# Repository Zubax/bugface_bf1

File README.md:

# Zubax BugFace BF1

Zubax BugFace BF1 (formerly known as Dronecode Probe) is a generic JTAG/SWD+UART console adapter compatible with most ARM Cortex based designs and in particular with the hardware maintained by the [Dronecode project](http://dronecode.org/).

The design is based on Black Magic Probe and is distributed under open source licenses. The full description of its features and supported targets can be found at the [Black Magic Probe homepage](https://black-magic.org/).

For the manufacturing instructions refer to [MANUFACTURING.md](MANUFACTURING.md).

## Features

- Some of the supported targets include:
  - STMicroelectronics STM32
  - Microchip/Atmel SAM
  - NXP LPC/Kinetis
  - Texas Instruments LM/TM
  - Silicon Labs EFM32/EZR32
  - Xilinx Zynq-7000
  - Broadcom BCM2836
  - **And many others!** See the [Black Magic Probe homepage](https://black-magic.org/) for the full list of supported targets.

- Embedded GDB server on the device. No host-side driver needed (this is unlike, for example, OpenOCD).
  - Loading the application into flash or RAM.
  - Real-time execution and single-stepping.
  - Hardware assisted breakpoints and read/write/access watchpoints.
  - Software breakpoints when executing from RAM.

- Simple integration with development tools and IDE.
- Connectors are compatible with the Dronecode Autopilot Connector Standard.
- Optional power supply delivery to the target (the power is sourced from USB).

## USB interface

BF1 is a composite USB device that incorporates two virtual serial port interfaces:

1. The first virtual serial port interface is connected to the debugger's embedded GDB server; this interface is used by the host-side debugger to interact with the target. The baud rate and other parameters of a typical serial port are irrelevant for this interface, because it has no physical representation.

2. The second virtual serial port interface is connected to the physical UART interface that can be used to communicate directly with the target's application (for example, this can be used to access the [Serial command line interface (Serial CLI)](https://wiki.zubax.com/public/serial-cli) on the target).

For example, the host may represent the debugger as follows:

- `COM3` (on Windows), or `/dev/serial/by-id/usb-Black_Magic_Debug_Black_Magic_Probe_v1.10.0-836-g254bc265-dirty_C0E079F1-if00` (on GNU/Linux) - this is the GDB interface.
- `COM4` (on Windows), or `/dev/serial/by-id/usb-Black_Magic_Debug_Black_Magic_Probe_v1.10.0-836-g254bc265-dirty_C0E079F1-if02` (on GNU/Linux) - this is the physical UART interface that can be used to interact with the target's application (e.g. a serial CLI).

The device does not require drivers since it uses the standard USB CDC ACM profile. If you're using the device with GNU/Linux, be sure [configure the access permissions correctly](https://wiki.zubax.com/en/public/USB/Using-USB-devices-with-GNULinux).

The USB Vendor ID (VID) is **0x1D50**, and the Product ID (PID) is **0x6018**.

## Connectors

This section documents the available debug interfaces and their connectors, except for the micro-USB since its purpose is evident.

### DCD-M

The DCD-M connector pinout is documented in the table below. It exposes both SWD and UART interfaces to the target, where UART is typically used to access the debug serial console of the target.

| Pin     | Type     | Name     | Comment           |
| ------- | -------- | -------- | ----------------- |
| 1       | IN       | `TPWR`   | Target power sense; also can be used to power the target. |
| 2       | IN       | `UART_RX`| Serial input.     |
| 3       | OUT      | `UART_TX`| Serial output.    |
| 4       | IN/OUT   | `SWDIO`  | SWD data line.    |
| 5       | OUT      | `SWDCLK` | SWD clock line.   |
| 6       | GND      | `GND`    |                   |

The connector part numbers are as follows:

| Name      | Manufacturer  | Part number                                                           | Pitch | Datasheet     |
| --------- | ------------- | --------------------------------------------------------------------- | ------| ------------- |
| DCD-M     | JST           | **BM06B-SRSS-TB** *(top entry)*, or **SM06B-SRSS-TB** *(side entry)*  | 1 mm  | [http://www.jst-mfg.com/product/pdf/eng/eSH.pdf](http://www.jst-mfg.com/product/pdf/eng/eSH.pdf) |

### ARM Cortex M debug connector

This is the standard ARM Cortex M debug connector that can be seen on many other ARM debuggers.

| Pin | Name            |
| --- | --------------- |
| 1   | `TPWR`          |
| 2   | `SWDIO/TMS`     |
| 3   | `GND`           |
| 4   | `SWDCLK/TCK`    |
| 5   | `GND`           |
| 6   | `SWO/TDO`       |
| 7   |                 |
| 8   | `NC/TDI`        |
| 9   | `GND`           |
| 10  | `nRESET`        |

### Pixhawk v1 serial

This connector exposes only the UART interface. It can be used as a general UART port, and its pinout is compatible with the debug serial port on the Pixhawk v1 autopilot.

| Pin | Type        | Name      | Comment   |
| --- | ----------- | --------- | --------- |
| 1   | Power OUT   | `5V`      | Optional 5 V supply output to the target directly from USB.<br><br>Disabled by default; refer to the schematic to see what hardware modifications are required to enable it. |
| 2   |             |           | Not used          |
| 3   |             |           | Not used          |
| 4   | IN          | `UART_RX` | Serial input      |
| 5   | OUT         | `UART_TX` | Serial output     |
| 6   | GND         | GND       |                   |

## Updating the device's own firmware

Please refer to the following sources:

- <https://black-magic.org/upgrade.html>
- [MANUFACTURING.md](MANUFACTURING.md)

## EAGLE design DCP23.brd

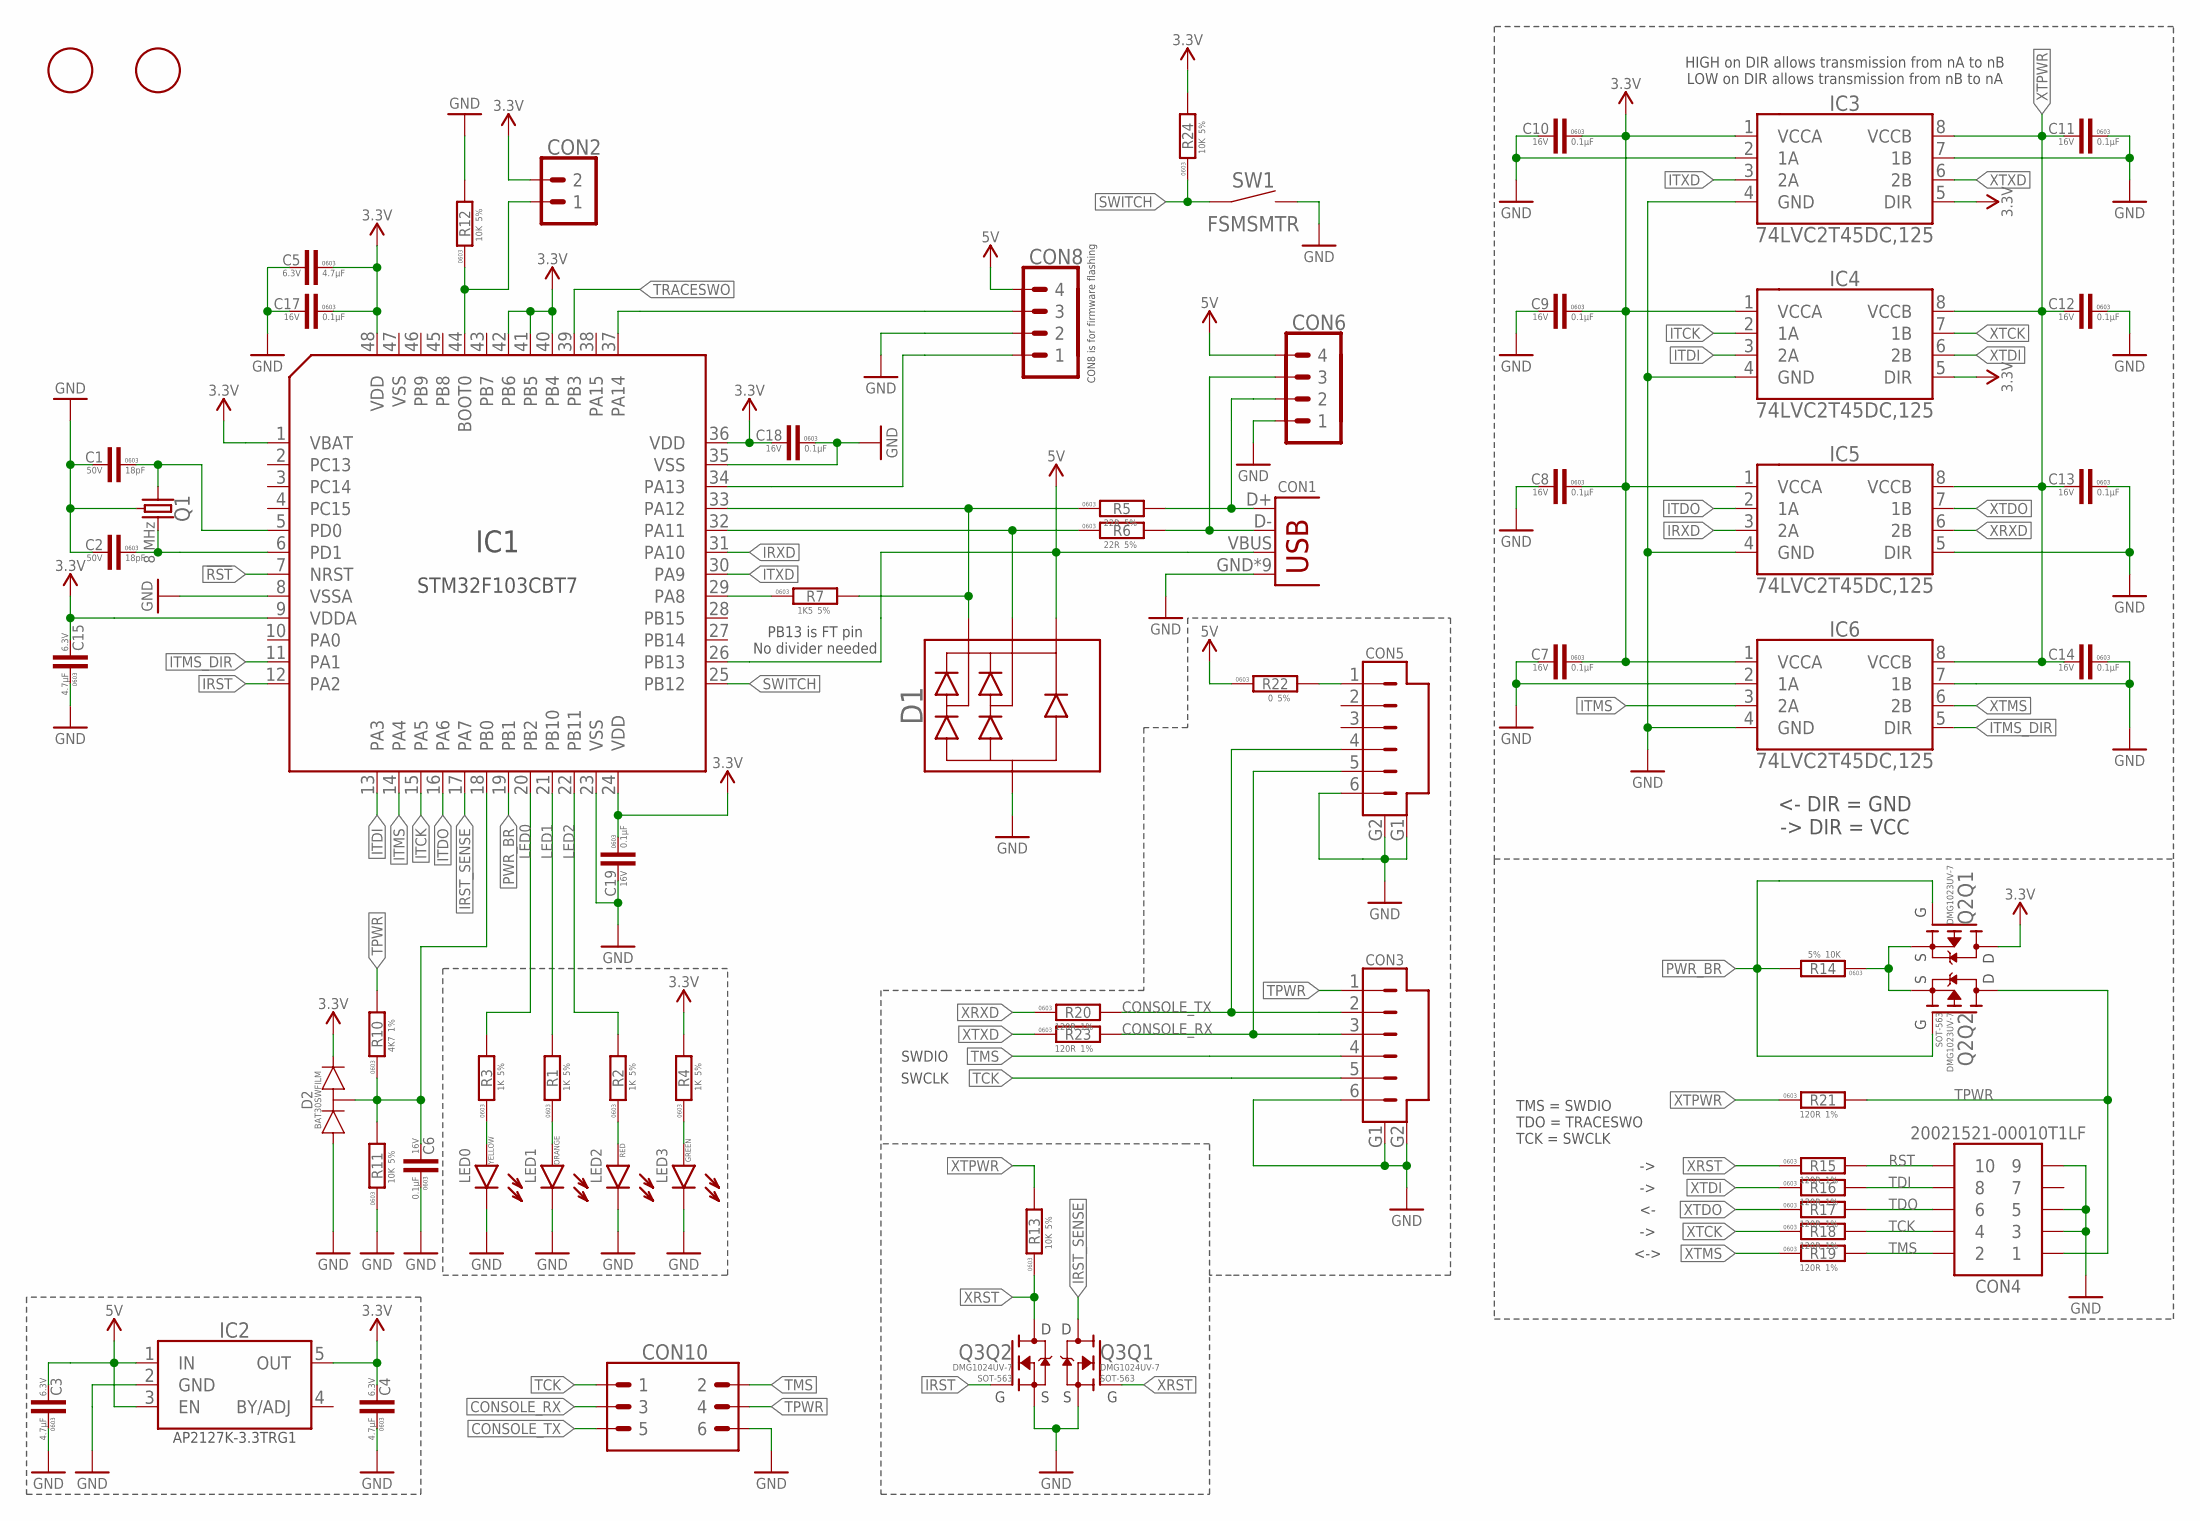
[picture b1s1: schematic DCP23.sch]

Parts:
C1, C2: 18pF; C0603
C3, C4, C5, C15: 4.7µF; C0603
C6, C7, C8, C9, C10, C11, C12, C13, C14, C17, C18, C19: 0.1µF; C0603
CON1: USB-1; MICRO_USB_WITH_PEGS
CON2: PINHEAD_1X02-2; 1X02-PTH-2
CON3: CON-6P-SM06B; SM06B
CON4: CON-2X5P; 200215-00010T1LF
CON5: CON-6P-DF13; DF13C-6P-1.25V
CON6, CON8: PINHEAD_1X04-2.54; 1X04-PTH-2.54
CON10: PINHEAD_2X03-PTH-2.54; 2X03-PTH-2.54
D1: PRTR5V0U2X; SOT143B
D2: BAT30SWFILM; SC70
IC1: STM32F103CBT7; LQFP48
IC2: AP2127-3.3; SOT23-5
IC3, IC4, IC5, IC6: 74LVC2T45; VSSOP8
LED0: LED-0603; LED0603; DIGIKEY# 160-1448-1-ND
LED1: LED-0603; LED0603; DIGIKEY# 160-1445-1-ND
LED2: LED-0603; LED0603; DIGIKEY# SML-D12U1WT86CT-ND
LED3: LED-0603; LED0603; DIGIKEY# 160-1446-1-ND
Q1: 8 MHz; OSCILLATOR-5.0X3.2-4P
Q2: DMG1023UV-7; SOT-563
Q3: DMG1024UV-7; SOT-563
R1, R2, R3, R4: 1K; R0603
R5, R6: 22R; R0603; DIGIKEY# 311-22NCT-ND
R7: 1K5; R0603; DIGIKEY# 311-1.50KHRCT-ND
R10: 4K7; R0603
R11, R12, R13, R14, R24: 10K; R0603
R15, R16, R17, R18, R19, R20, R21, R23: 120R; R0603
R22: 0; R0603
SW1: TACT_SWITCH-FSMSM; FSMSM
U$9, U$10: FIDUCIALMOUNT; FIDUCIA-MOUNT

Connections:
!RST: IC1.7 (NRST)
CONSOLE_RX: CON3.3, CON5.5, CON10.3, R23.P$2 (2)
CONSOLE_TX: CON3.2, CON5.4, CON10.5, R20.P$2 (2)
GND: C1.P$2 (2), C2.P$2 (2), C3.P$1 (1), C4.P$1 (1), C5.P$2 (2), C6.P$1 (1), C7.P$2 (2), C8.P$2 (2), C9.P$2 (2), C10.P$2 (2), C11.P$1 (1), C12.P$1 (1), C13.P$1 (1), C14.P$1 (1), C15.P$1 (1), C17.P$2 (2), C18.P$1 (1), C19.P$2 (2), CON1.GND, CON1.GND1 (GND), CON1.GND2 (GND), CON1.GND3 (GND), CON1.GND4 (GND), CON1.P$1 (GND), CON1.P$2 (GND), CON1.P$3 (GND), CON1.P$4 (GND), CON3.6, CON3.G1, CON3.G2, CON4.3, CON4.5, CON4.9, CON5.6, CON5.G1 (G2), CON5.G2 (G1), CON6.1, CON8.2, CON10.6, D1.1 (C), D2.1 (A), IC1.8 (VSSA), IC1.23 (VSS), IC1.35 (VSS), IC2.2 (GND), IC3.2 (1A), IC3.4 (GND), IC3.7 (1B), IC4.4 (GND), IC5.4 (GND), IC5.5 (DIR), IC6.2 (1A), IC6.4 (GND), IC6.7 (1B), LED0.C, LED1.C, LED2.C, LED3.C, Q1.2 (GND), Q1.4 (GND), Q3.1 (S), Q3.4 (S), R11.P$1 (1), R12.P$2 (2), SW1.P$2 (2)
IRST: IC1.12 (PA2), Q3.5 (G)
IRST_SENSE: IC1.17 (PA7), Q3.6 (D)
IRXD: IC1.31 (PA10), IC5.3 (2A)
ITCK: IC1.15 (PA5), IC4.2 (1A)
ITDI: IC1.13 (PA3), IC4.3 (2A)
ITDO: IC1.16 (PA6), IC5.2 (1A)
ITMS: IC1.14 (PA4), IC6.3 (2A)
ITMS_DIR: IC1.11 (PA1), IC6.5 (DIR)
ITXD: IC1.30 (PA9), IC3.3 (2A)
LED0: IC1.20 (PB2), R3.P$2 (2)
LED1: IC1.21 (PB10), R1.P$2 (2)
LED2: IC1.22 (PB11), R2.P$2 (2)
unnamed: C1.P$1 (1), IC1.5 (PD0), Q1.1
unnamed: LED0.A, R3.P$1 (1)
unnamed: C2.P$1 (1), IC1.6 (PD1), Q1.3 (2)
unnamed: LED2.A, R2.P$1 (1)
unnamed: LED1.A, R1.P$1 (1)
unnamed: LED3.A, R4.P$1 (1)
unnamed: IC1.29 (PA8), R7.1
unnamed: D1.3 (D2), IC1.32 (PA11), R6.1
unnamed: D1.2 (D1), IC1.33 (PA12), R5.1, R7.2
unnamed: Q2.1 (S), Q2.4 (S), R14.P$1 (1)
unnamed: CON5.1, R22.P$2 (2)
unnamed: CON2.1, IC1.44 (BOOT0), R12.P$1 (1)
PWR_BR: IC1.19 (PB1), Q2.2 (G), Q2.5 (G), R14.P$2 (2)
RST: CON4.10, R15.P$2 (2)
SWCLK: CON8.3, IC1.37 (PA14)
SWDIO: CON8.1, IC1.34 (PA13)
SWITCH: IC1.25 (PB12), R24.P$1 (1), SW1.P$1 (1)
TCK: CON3.5, CON4.4, CON10.1, R18.P$2 (2)
TDI: CON4.8, R16.P$2 (2)
TDO: CON4.6, R17.P$2 (2)
TMS: CON3.4, CON4.2, CON10.2, R19.P$2 (2)
TPWR: CON3.1, CON4.1, CON10.4, Q2.6 (D), R10.P$2 (2), R21.P$2 (2)
TRACESWO: IC1.39 (PB3)
USB_DM: CON1.D-, CON6.3, R6.2
USB_DP: CON1.D+, CON6.2, R5.2
VBUS1: C6.P$2 (2), D2.3 (COMMON), IC1.18 (PB0), R10.P$1 (1), R11.P$2 (2)
VDD_3V3: C4.P$2 (2), C5.P$1 (1), C7.P$1 (1), C8.P$1 (1), C9.P$1 (1), C10.P$1 (1), C15.P$2 (2), C17.P$1 (1), C18.P$2 (2), C19.P$1 (1), CON2.2, D2.2 (C), IC1.1 (VBAT), IC1.9 (VDDA), IC1.24 (VDD), IC1.36 (VDD), IC1.40 (PB4), IC1.41 (PB5), IC1.42 (PB6), IC1.48 (VDD), IC2.5 (OUT), IC3.1 (VCCA), IC3.5 (DIR), IC4.1 (VCCA), IC4.5 (DIR), IC5.1 (VCCA), IC6.1 (VCCA), Q2.3 (D), R4.P$2 (2), R24.P$2 (2)
VDD_5V: C3.P$2 (2), CON1.VBUS, CON6.4, CON8.4, D1.4 (A), IC1.26 (PB13), IC2.1 (IN), IC2.3 (EN), R22.P$1 (1)
XRST: Q3.2 (G), Q3.3 (D), R13.P$1 (1), R15.P$1 (1)
XRXD: IC5.6 (2B), R20.P$1 (1)
XTCK: IC4.7 (1B), R18.P$1 (1)
XTDI: IC4.6 (2B), R16.P$1 (1)
XTDO: IC5.7 (1B), R17.P$1 (1)
XTMS: IC6.6 (2B), R19.P$1 (1)
XTPWR: C11.P$2 (2), C12.P$2 (2), C13.P$2 (2), C14.P$2 (2), IC3.8 (VCCB), IC4.8 (VCCB), IC5.8 (VCCB), IC6.8 (VCCB), R13.P$2 (2), R21.P$1 (1)
XTXD: IC3.6 (2B), R23.P$1 (1)

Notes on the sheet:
<- DIR = GND -> DIR = VCC
TMS = SWDIO TDO = TRACESWO TCK = SWCLK
<->
HIGH on DIR allows transmission from nA to nB LOW on DIR allows transmission from nB to nA
SWDIO
SWCLK
CON8 is for firmware flashing
PB13 is FT pin No divider needed

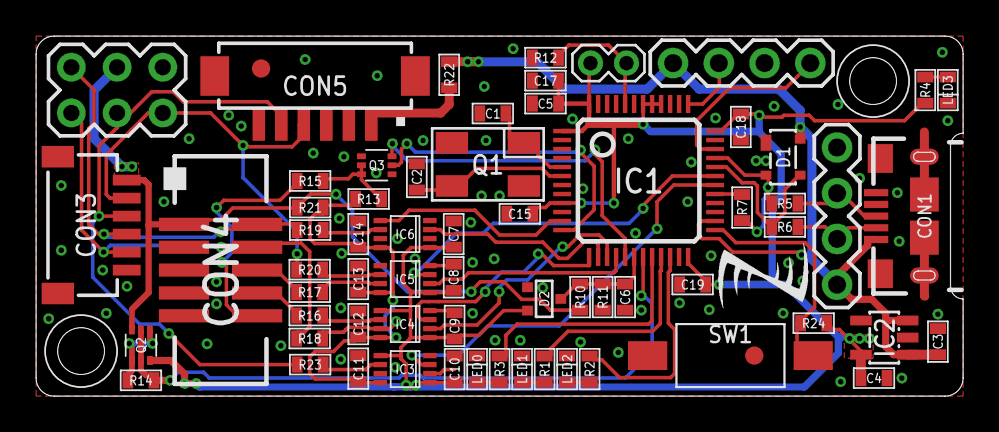
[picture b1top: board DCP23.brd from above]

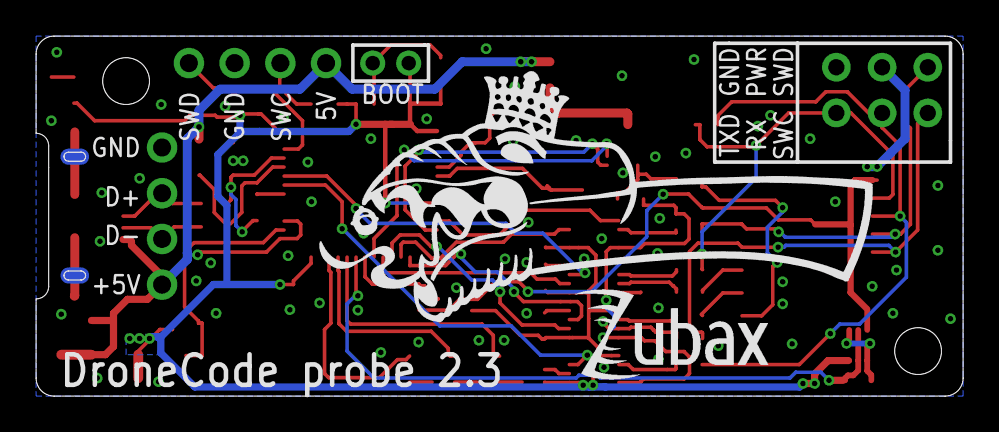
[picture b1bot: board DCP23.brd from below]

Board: 2 copper layers, 51.5 x 20.0 mm, 69 parts (2 on the bottom side), 50 nets.

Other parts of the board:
U$1: DRAGON-30X13
U$2: Z_LOGO_5
U$3: ZUBAX_LOGO_5X10

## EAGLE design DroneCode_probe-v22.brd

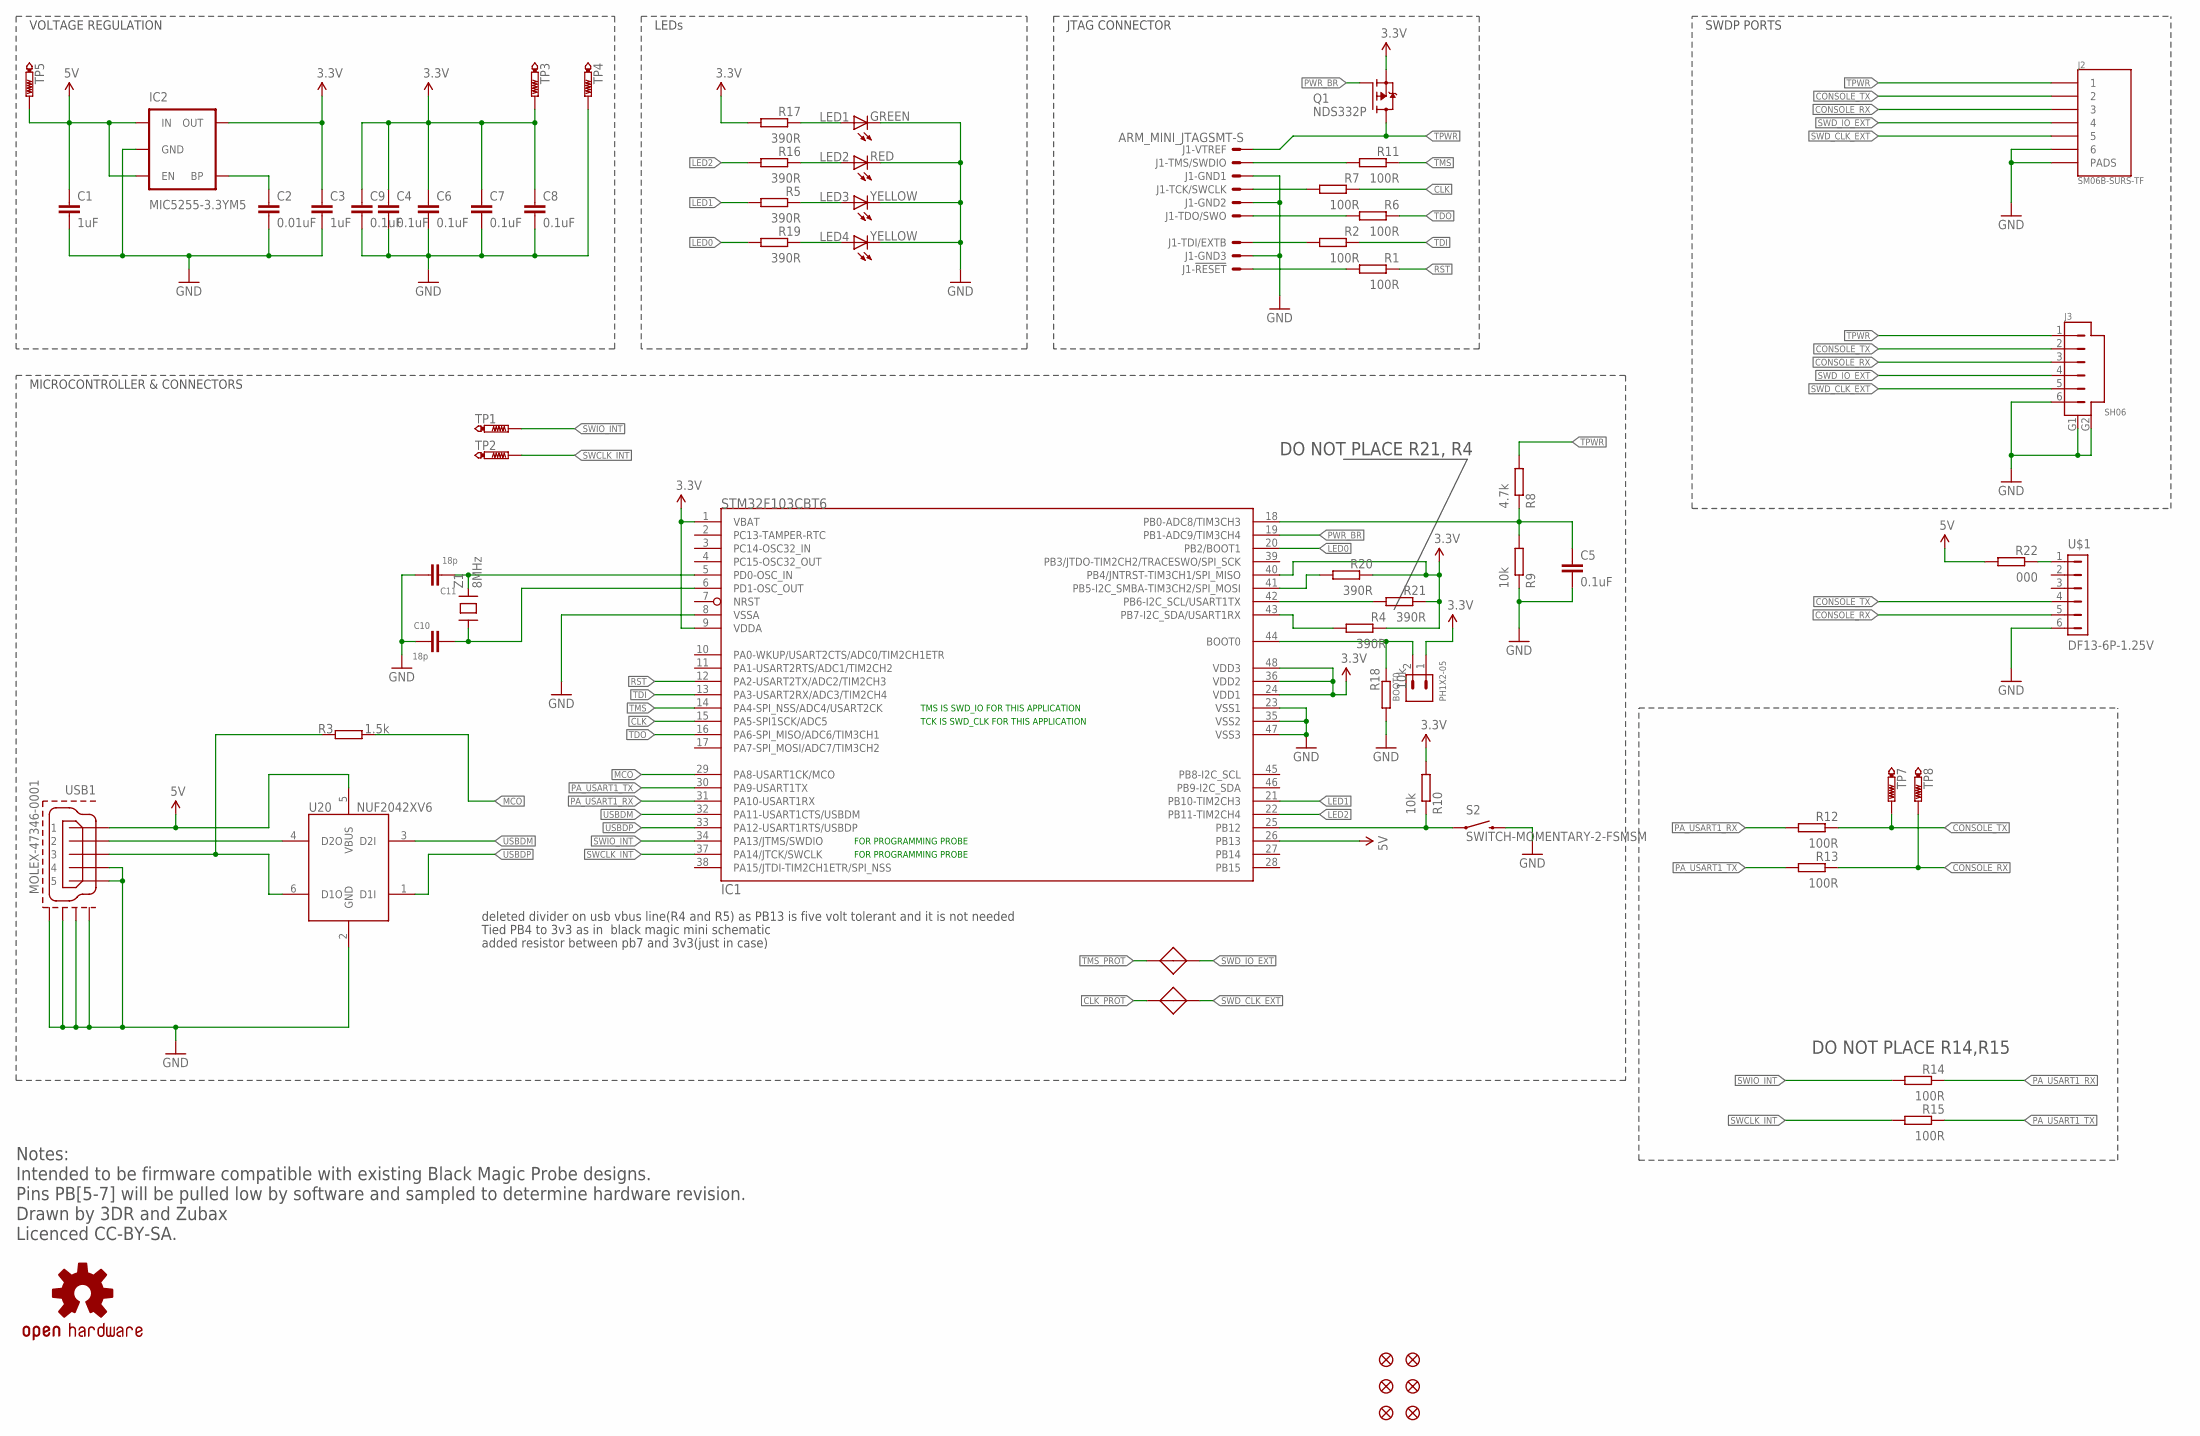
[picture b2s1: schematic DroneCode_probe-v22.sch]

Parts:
BOOT0: PH1X2-05; PH005-1-2
C1, C3: 1uF; 0603-CAP; PARTNO CC0603ZRY5V7BB105; DIGIKEY# 311-1372-1-ND
C2: 0.01uF; 0402-CAP; PARTNO EMK105B7103KV-F; DIGIKEY# 587-2708-1-ND
C4, C5, C6, C7, C8, C9: 0.1uF; 0402-CAP; PARTNO C1005X7R1E104K050BB; DIGIKEY# 445-7348-1-ND
C10, C11: 18p; 0402; DIGIKEY# CL05C180JB5NNNC
IC1: STM32F103CBT6; LQFP48; PARTNO STM32F103CBT6; DIGIKEY# 497-6288-ND
IC2: MIC5255-3.3YM5; SOT23-5; PARTNO MIC5255-3.3YM5 TR; DIGIKEY# 576-1290-1-ND
J1: ARM_MINI_JTAGSMT-S; 200215-00010T1LF; PARTNO 20021521-00010T1LF; DIGIKEY# 609-4054-ND
J2: SM06B-SURS-TF; SM02B-SURS-TF; PARTNO SM06B-SURS-TF(LF)(SN); DIGIKEY# SM06B-SURS-TF(LF)(SN)-ND
J3: SH06; SH06B; PARTNO SM06B-SRSS-TB; DIGIKEY# 455-1806-1-ND
J4, J5: JUNCTION
JP1, JP2, JP3, JP4, JP5, JP6: FIDUCIAL1X2; FIDUCIAL-1X2
LED1: GREEN; 0603-LED; PARTNO APT1608SGC; DIGIKEY# 754-1121-1-ND
LED2: RED; 0603-LED; PARTNO APT1608SRCPRV; DIGIKEY# 754-1122-1-ND
LED3, LED4: YELLOW; 0603-LED; PARTNO APT1608YC; DIGIKEY# 754-1125-1-ND
Q1: NDS332P; SOT23B-3
R1, R2, R6, R7, R11, R12, R13, R14, R15: 100R; 0402-RES; PARTNO RC0402FR-07100RL; DIGIKEY# 311-100LRCT-ND
R3: 1.5k; 0402-RES; PARTNO RC0402FR-071K5L; DIGIKEY# 311-1.50KLRCT-ND
R4, R5, R16, R17, R19, R20, R21: 390R; 0402-RES; PARTNO CRCW0402390RJNED; DIGIKEY# 541-390JCT-ND
R8: 4.7k; 0402-RES; PARTNO ERJ-2RKF4701X; DIGIKEY# P4.70KLCT-ND
R9, R10, R18: 10k; 0402-RES; PARTNO RC0402FR-0710KL; DIGIKEY# 311-10.0KLRCT-ND
R22: 000; 0402-RES; PARTNO ERJ-2GE0R00X; DIGIKEY# P0.0JCT-ND
S2: SWITCH-MOMENTARY-2-FSMSM; FSMSM
TP1, TP2, TP3, TP4, TP5, TP7, TP8: PTR1B1,27; B1,27
U20: NUF2042XV6; SOT563-6; PARTNO NUF2042XV6T1G; DIGIKEY# NUF2042XV6T1GOSCT-ND
U$1: DF13-6P-1.25V; DF13C-6P-1.25V; PARTNO DF13C-6P-1.25V(20); DIGIKEY# H3423-ND
U$5: OSHW-LOGOL; OSHW-LOGO-L
USB1: MOLEX-47346-0001; PARTNO 47346-0001; DIGIKEY# WM17141CT-ND
Z1: 8MHz; NX3225GD

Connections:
3.3V: BOOT0.1, C3.P$1 (1), C4.P$1 (1), C6.P$1 (1), C7.P$1 (1), C8.P$1 (1), C9.P$1 (1), IC1.1 (VBAT), IC1.9 (VDDA), IC1.24 (VDD1), IC1.36 (VDD2), IC1.40 (PB4/JNTRST-TIM3CH1/SPI_MISO), IC1.48 (VDD3), IC2.5 (OUT), Q1.S, R4.P$1 (1), R10.P$2 (2), R17.P$2 (2), R20.P$1 (1), R21.P$1 (1), TP3.TP
5V: C1.P$1 (1), IC1.26 (PB13), IC2.1 (IN), IC2.3 (EN), R22.P$2 (2), TP5.TP, U20.5 (VBUS), USB1.VBUS (1)
CLK: IC1.15 (PA5-SPI1SCK/ADC5), R7.P$1 (1)
CLK_PROT: J1.4, J5.P$1 (1), R7.P$2 (2)
CONSOLE_RX: J2.3, J3.3, R13.P$1 (1), TP8.TP, U$1.5
CONSOLE_TX: J2.2, J3.2, R12.P$1 (1), TP7.TP, U$1.4
GND: C1.P$2 (2), C2.P$2 (2), C3.P$2 (2), C4.P$2 (2), C5.P$2 (2), C6.P$2 (2), C7.P$2 (2), C8.P$2 (2), C9.P$2 (2), C10.2, C11.1, IC1.8 (VSSA), IC1.23 (VSS1), IC1.35 (VSS2), IC1.47 (VSS3), IC2.2 (GND), J1.3, J1.5, J1.9, J2.6, J2.PAD-L (PADS), J2.PAD-R (PADS), J3.6, J3.G1, J3.G2, LED1.C, LED2.C, LED3.C, LED4.C, R9.P$1 (1), R18.P$2 (2), S2.P$2 (2), TP4.TP, U20.2 (GND), U$1.6, USB1.GND (5), USB1.GND1, USB1.GND2, USB1.GND3, USB1.GND4, USB1.ID (4)
LED0: IC1.20 (PB2/BOOT1), R19.P$2 (2)
LED1: IC1.21 (PB10-TIM2CH3), R5.P$2 (2)
LED2: IC1.22 (PB11-TIM2CH4), R16.P$2 (2)
MCO: IC1.29 (PA8-USART1CK/MCO), R3.P$2 (2)
unnamed: U20.4 (D2O), USB1.D- (2)
unnamed: C2.P$1 (1), IC2.4 (BP)
unnamed: R3.P$1 (1), U20.6 (D1O), USB1.D+ (3)
unnamed: IC1.43 (PB7-I2C_SDA/USART1RX), R4.P$2 (2)
unnamed: BOOT0.2, IC1.44 (BOOT0), R18.P$1 (1)
unnamed: R22.P$1 (1), U$1.1
unnamed: IC1.41 (PB5-I2C_SMBA-TIM3CH2/SPI_MOSI), R20.P$2 (2)
unnamed: IC1.42 (PB6-I2C_SCL/USART1TX), R21.P$2 (2)
unnamed: C5.P$1 (1), IC1.18 (PB0-ADC8/TIM3CH3), R8.P$1 (1), R9.P$2 (2)
unnamed: IC1.25 (PB12), R10.P$1 (1), S2.P$1 (1)
unnamed: LED1.A, R17.P$1 (1)
unnamed: LED2.A, R16.P$1 (1)
unnamed: LED3.A, R5.P$1 (1)
unnamed: LED4.A, R19.P$1 (1)
unnamed: C11.2, IC1.5 (PD0-OSC_IN), Z1.2
unnamed: C10.1, IC1.6 (PD1-OSC_OUT), Z1.1
PA_USART1_RX: IC1.31 (PA10-USART1RX), R12.P$2 (2), R14.P$1 (1)
PA_USART1_TX: IC1.30 (PA9-USART1TX), R13.P$2 (2), R15.P$1 (1)
PWR_BR: IC1.19 (PB1-ADC9/TIM3CH4), Q1.G
RST: IC1.12 (PA2-USART2TX/ADC2/TIM2CH3), R1.P$1 (1)
RST_PROT: J1.10, R1.P$2 (2)
SWCLK_INT: IC1.37 (PA14/JTCK/SWCLK), R15.P$2 (2), TP2.TP
SWD_CLK_EXT: J2.5, J3.5, J5.P$2 (2)
SWD_IO_EXT: J2.4, J3.4, J4.P$2 (2)
SWIO_INT: IC1.34 (PA13/JTMS/SWDIO), R14.P$2 (2), TP1.TP
TDI: IC1.13 (PA3-USART2RX/ADC3/TIM2CH4), R2.P$1 (1)
TDI_PROT: J1.8, R2.P$2 (2)
TDO: IC1.16 (PA6-SPI_MISO/ADC6/TIM3CH1), R6.P$1 (1)
TDO_PROT: J1.6, R6.P$2 (2)
TMS: IC1.14 (PA4-SPI_NSS/ADC4/USART2CK), R11.P$1 (1)
TMS_PROT: J1.2, J4.P$1 (1), R11.P$2 (2)
TPWR: J1.1, J2.1, J3.1, Q1.D, R8.P$2 (2)
USBDM: IC1.32 (PA11-USART1CTS/USBDM), U20.3 (D2I)
USBDP: IC1.33 (PA12-USART1RTS/USBDP), U20.1 (D1I)

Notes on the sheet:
Notes: Intended to be firmware compatible with existing Black Magic Probe designs. Pins PB[5-7] will be pulled low by software and sampled to determine hardware revision. Drawn by 3DR and Zubax Licenced CC-BY-SA.
VOLTAGE REGULATION
LEDs
JTAG CONNECTOR
MICROCONTROLLER & CONNECTORS
FOR PROGRAMMING PROBE
TCK IS SWD_CLK FOR THIS APPLICATION
TMS IS SWD_IO FOR THIS APPLICATION
SWDP PORTS
deleted divider on usb vbus line(R4 and R5) as PB13 is five volt tolerant and it is not needed
Tied PB4 to 3v3 as in black magic mini schematic
added resistor between pb7 and 3v3(just in case)
DO NOT PLACE R14,R15
DO NOT PLACE R21, R4

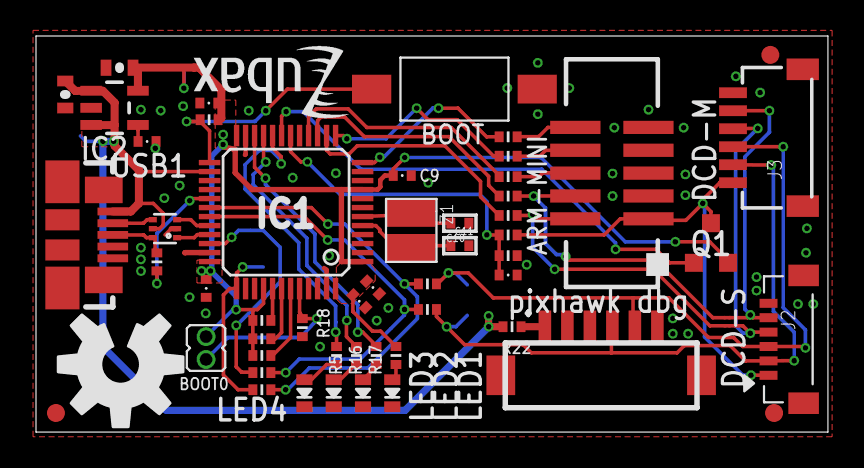
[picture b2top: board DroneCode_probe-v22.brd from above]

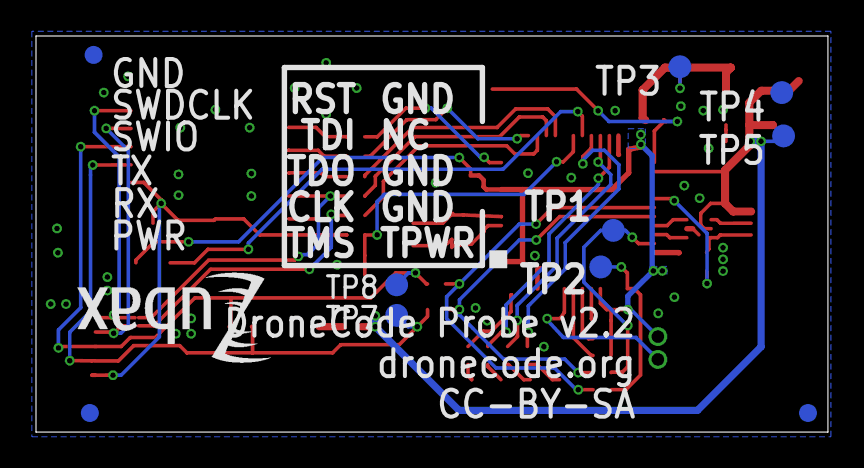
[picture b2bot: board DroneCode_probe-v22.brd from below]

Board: 2 copper layers, 44.0 x 22.0 mm, 67 parts (11 on the bottom side), 45 nets.

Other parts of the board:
U$7: ZUBAX_LOGO_4X8
U$8: ZUBAX_LOGO_5X10

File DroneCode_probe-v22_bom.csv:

Qty	Value	Device	Package	Parts	DIGIKEY#	PARTNO	Description
1	0.01uF	CAP-0402	0402-CAP	C2	587-2708-1-ND	EMK105B7103KV-F	
6	0.1uF	CAPACITOR-0402	0402-CAP	C4, C5, C6, C7, C8, C9	445-7348-1-ND	C1005X7R1E104K050BB	
1	000	RESISTOR-0402	0402-RES	R22	P0.0JCT-ND	ERJ-2GE0R00X	
1	1.5k	RESISTOR-0402	0402-RES	R3	311-1.50KLRCT-ND	RC0402FR-071K5L	
7	100R	RESISTOR-0402	0402-RES	R1, R2, R6, R7, R11, R12, R13	311-100LRCT-ND	RC0402FR-07100RL	
3	10k	RESISTOR-0402	0402-RES	R9, R10, R18	311-10.0KLRCT-ND	RC0402FR-0710KL	
2	18p	C0402	402	C10, C11	CL05C180JB5NNNC	CL05C180JB5NNNC	
2	1uF	CAPACITOR-0603	0603-CAP	C1, C3	311-1372-1-ND	CC0603ZRY5V7BB105	
5	390R	RESISTOR-0402	0402-RES	R5, R16, R17, R19, R20	541-390JCT-ND	CRCW0402390RJNED	
1	4.7k	RESISTOR-0402	0402-RES	R8	P4.70KLCT-ND	ERJ-2RKF4701X	
1	8MHz	CRYSTAL-NX3225GD	NX3225GD	Z1	644-1178-1-ND	NX3225GD-8MHZ-STD-CRA-3	SMD CRYSTAL
1	ARM_MINI_JTAGSMT-S	ARM_MINI_JTAGSMT-S	200215-00010T1LF	J1	609-4054-ND	20021521-00010T1LF	CONNECTOR
1	DF13-6P-1.25V	DF13-6P-1.25V	DF13C-6P-1.25V	U$1	H3423-ND	DF13C-6P-1.25V(20)	DF13-6P
1	GREEN	LED-0603	0603-LED	LED1	754-1121-1-ND	APT1608SGC	
1	MIC5255-3.3YM5	V_REG_LDOSMD	SOT23-5	IC2	576-1290-1-ND	MIC5255-3.3YM5 TR	Voltage Regulator LDO
1	MOLEX-47346-0001	MOLEX-47346-0001	MOLEX-47346-0001	USB1	WM17141CT-ND	47346-0001	MICRO USB B, BOTTOM MOUNT
1	NDS332P	NDS332P	SOT23B-3	Q1	NDS332PCT-ND	NDS332P	MOSFET P-CH 20V 1A SSOT3
1	NUF2042XV6	NUF2042XV6	SOT563-6	U20	NUF2042XV6T1GOSCT-ND	NUF2042XV6T1G	
1	RED	LED-0603	0603-LED	LED2	754-1122-1-ND	APT1608SRCPRV	red smd led
1	SH06	SH06	SH06B	J3	455-1806-1-ND	SM06B-SRSS-TB	
1	SM06B-SURS-TF	SM06B-SURS-TF	SM02B-SURS-TF	J2	SM06B-SURS-TF(LF)(SN)-ND	SM06B-SURS-TF(LF)(SN)	
1	STM32F103CBT6	STM32F102CBT6	LQFP48	IC1	497-6288-ND	STM32F103CBT6	STM32F103 Medium Density 48pins
1	SWITCH-MOMENTARY-2-FSMSM	SWITCH-MOMENTARY-2-FSMSM	FSMSM	S2	450-1140-ND	FSMSM	SWITCH TACTILE SPST-NO 0.05A 24V
2	YELLOW	LED-0603	0603-LED	LED3, LED4	754-1125-1-ND	APT1608YC	yellow smd led

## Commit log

2015-07-30 BOM converted to CSV
2015-08-04 CSV formatting fix - comments removed
2015-08-04 Rename DroneCode_probe-v22_bom.csv to DroneCode_probe-v22_bom.tsv
2015-08-06 Cable sources
2015-08-06 README cleanup
2015-09-21 -Added assembly file
2015-09-27 Manufacturing instructions
2015-09-28 Elaborated MANUFACTURING.md
2015-10-31 Added links to README
2015-11-17 MANUFACTURING.md - link to prebuilt binaries
2016-05-18 Fixed typo in BOM
    Schematic also needs update
2017-02-15 -added gerber files
2019-01-28 cleanup
2019-02-05 udpates
2019-02-05 let the doc be here
2019-02-05 blah
2019-02-06 2.3 schematic completed
2019-02-06 DRU file added
2019-02-06 Some routing
2019-02-07 more routing
2019-02-07 more routong
2019-02-13 DroneCode probe V2.3
2019-03-21 MANUFACTURING instructions are back
2019-03-25 Update MANUFACTURING.md
    specially fo Pavel
2019-03-25 Remove DCD-S from README since we no longer support it
2019-04-26 3d model import
2023-10-31 smoll fix
2023-10-31 Update documentation (#8)
2024-04-02 udpate readme
2024-07-31 Update the docs
2024-07-31 Move imgs
2024-07-31 update readme (#9)
    move the kb page here from https://kb.zubax.com/display/MAINKB/Dronecode+Probe+documentation
    ---------
2024-07-31 Update branding
2025-05-18 update manufacturing instructions
2025-05-19 update the flashing script

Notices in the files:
parts and their libraries:
SparkFun: Licensing: CC v3.0 Share-Alike You are welcome to use this library for commercial purposes.
